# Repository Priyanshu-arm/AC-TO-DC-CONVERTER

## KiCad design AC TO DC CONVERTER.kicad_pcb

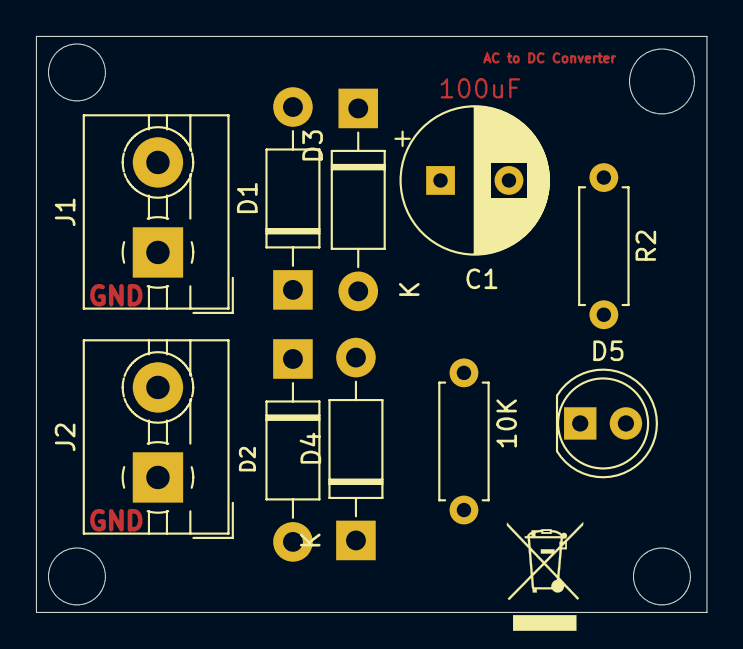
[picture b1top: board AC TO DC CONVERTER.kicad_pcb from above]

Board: 2 copper layers, 37.2 x 32.0 mm, 10 parts (0 on the bottom side), 5 nets.

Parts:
10K: 10K; R_Axial_DIN0207_L6.3mm_D2.5mm_P7.62mm_Horizontal
C1: C; CP_Radial_D8.0mm_P3.80mm
D1, D2, D3, D4: 1N4007; D_DO-41_SOD81_P10.16mm_Horizontal
D5: LED(5mm); LED_D5.0mm
J1: INPUT; TerminalBlock_MaiXu_MX126-5.0-02P_1x02_P5.00mm
J2: OUTPUT; TerminalBlock_MaiXu_MX126-5.0-02P_1x02_P5.00mm
R2: 2.2K; R_Axial_DIN0207_L6.3mm_D2.5mm_P7.62mm_Horizontal

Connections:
/+VE: 10K.2, C1.2, D3.2 (A), D4.2 (A), J2.2, R2.2
GND: 10K.1, C1.1, D1.1 (K), D2.1 (K), D5.1 (K), J2.1
unnamed: D1.2 (A), D3.1 (K), J1.2
unnamed: D2.2 (A), D4.1 (K), J1.1
unnamed: D5.2 (A), R2.1
